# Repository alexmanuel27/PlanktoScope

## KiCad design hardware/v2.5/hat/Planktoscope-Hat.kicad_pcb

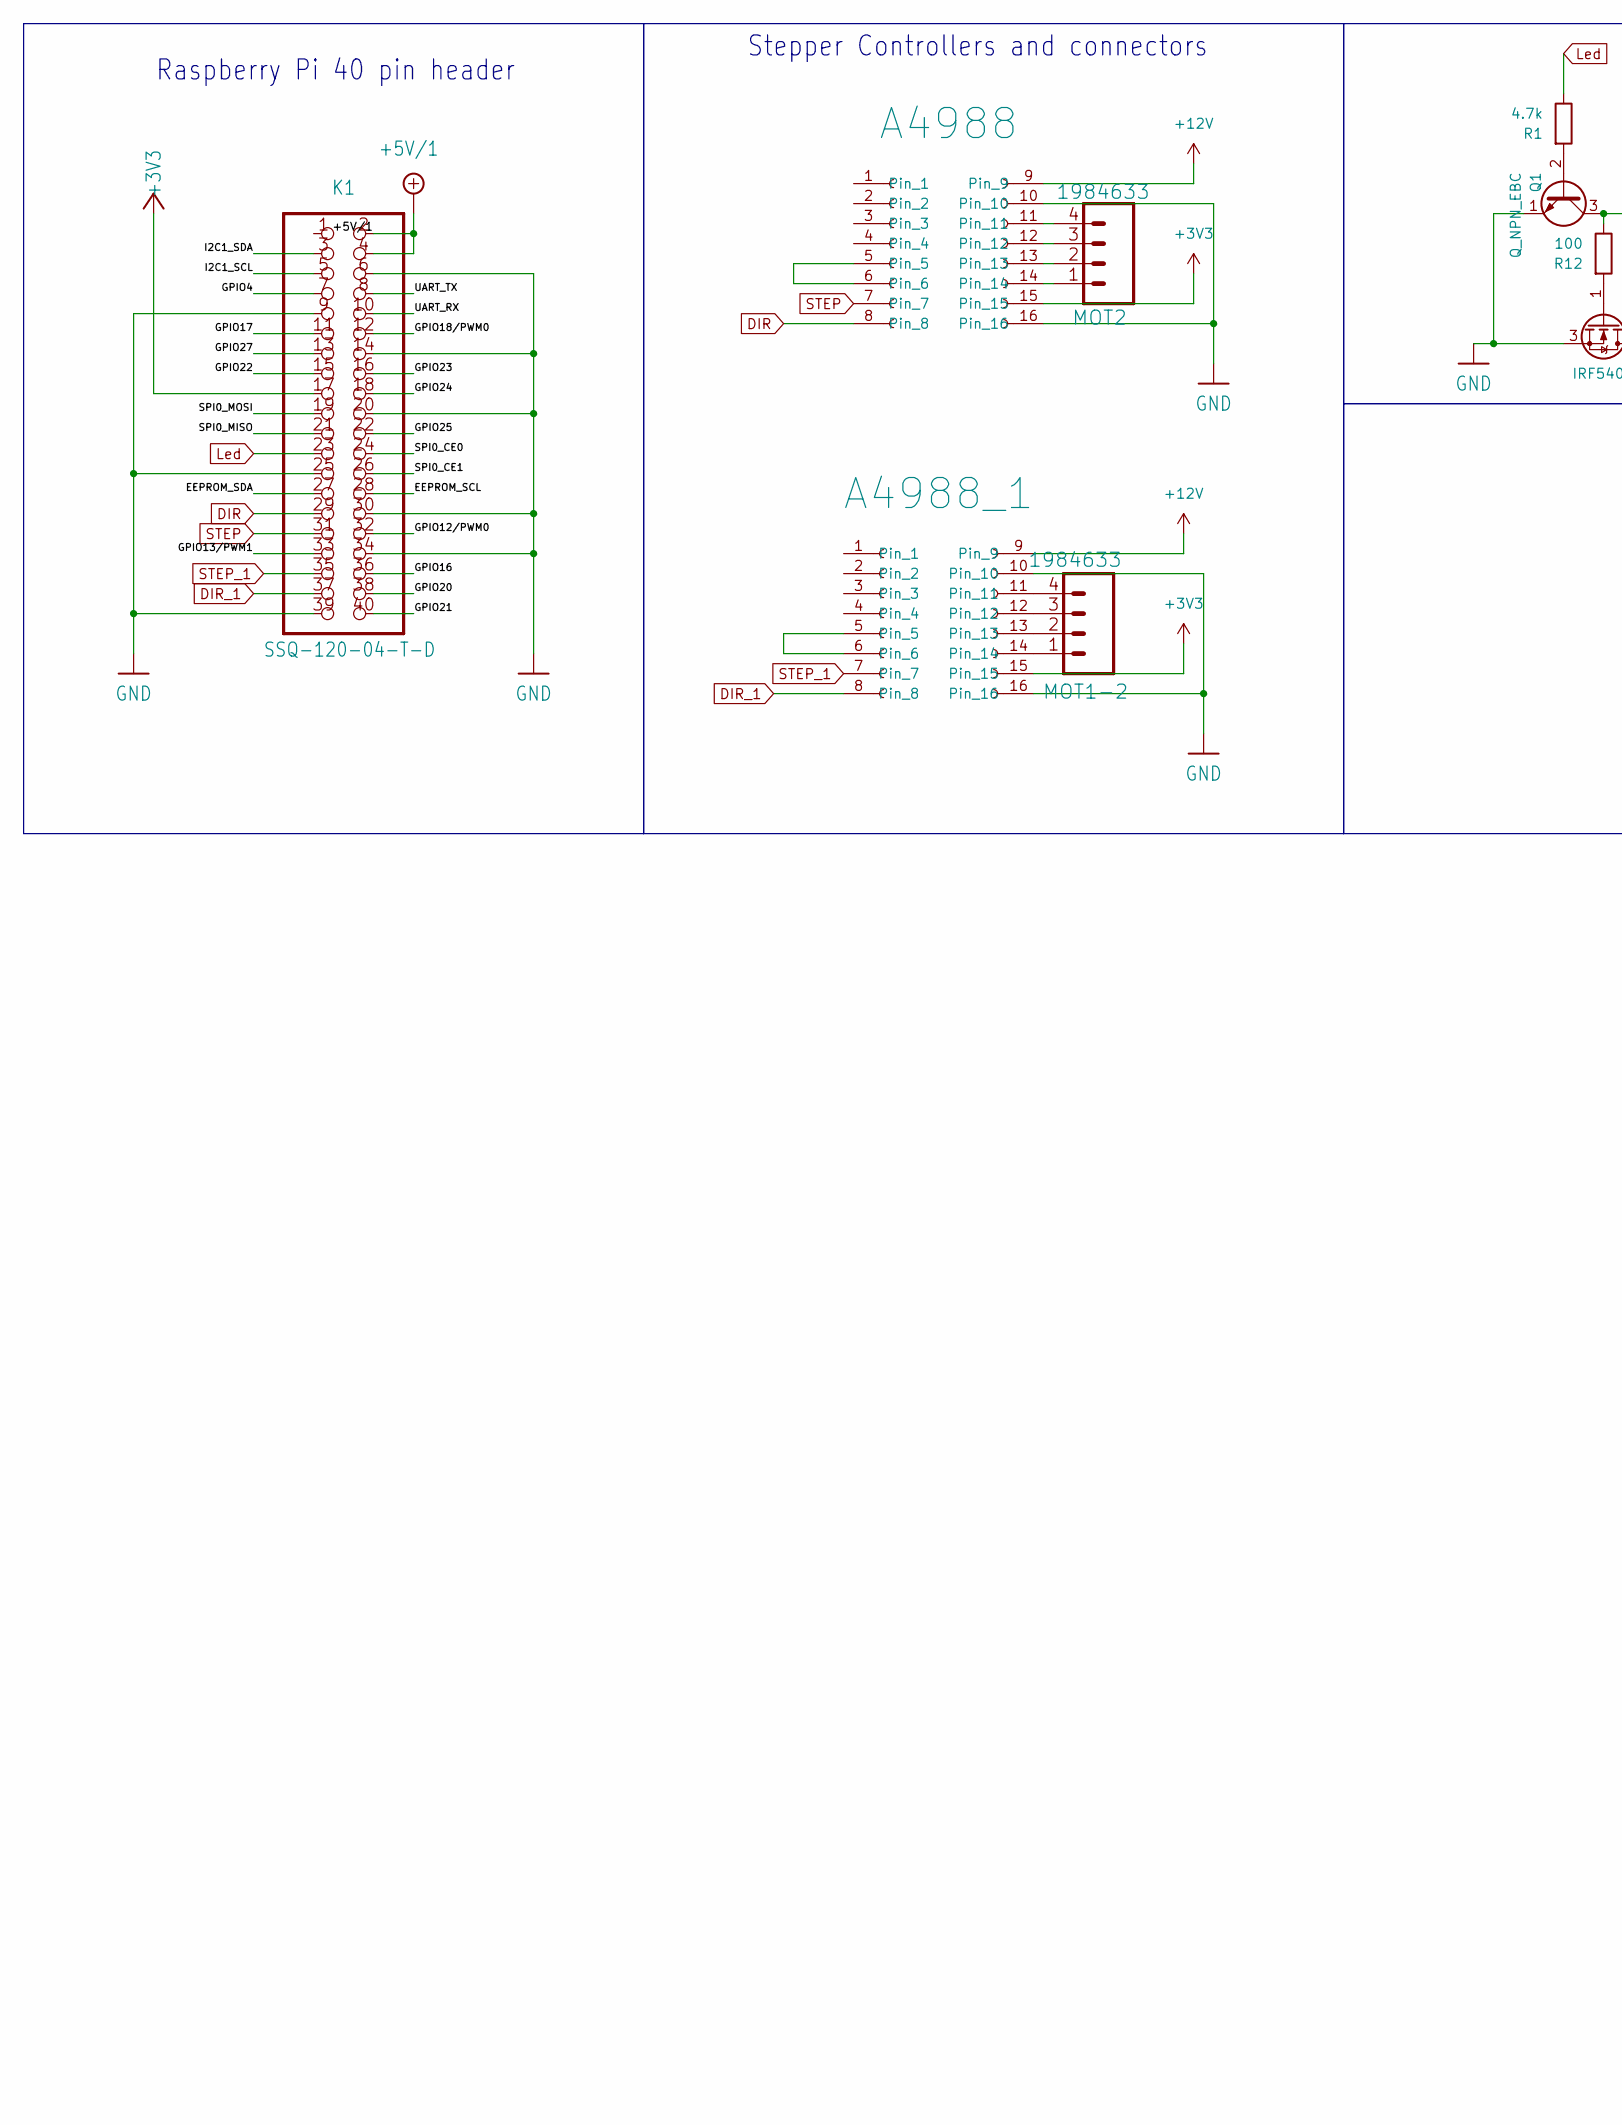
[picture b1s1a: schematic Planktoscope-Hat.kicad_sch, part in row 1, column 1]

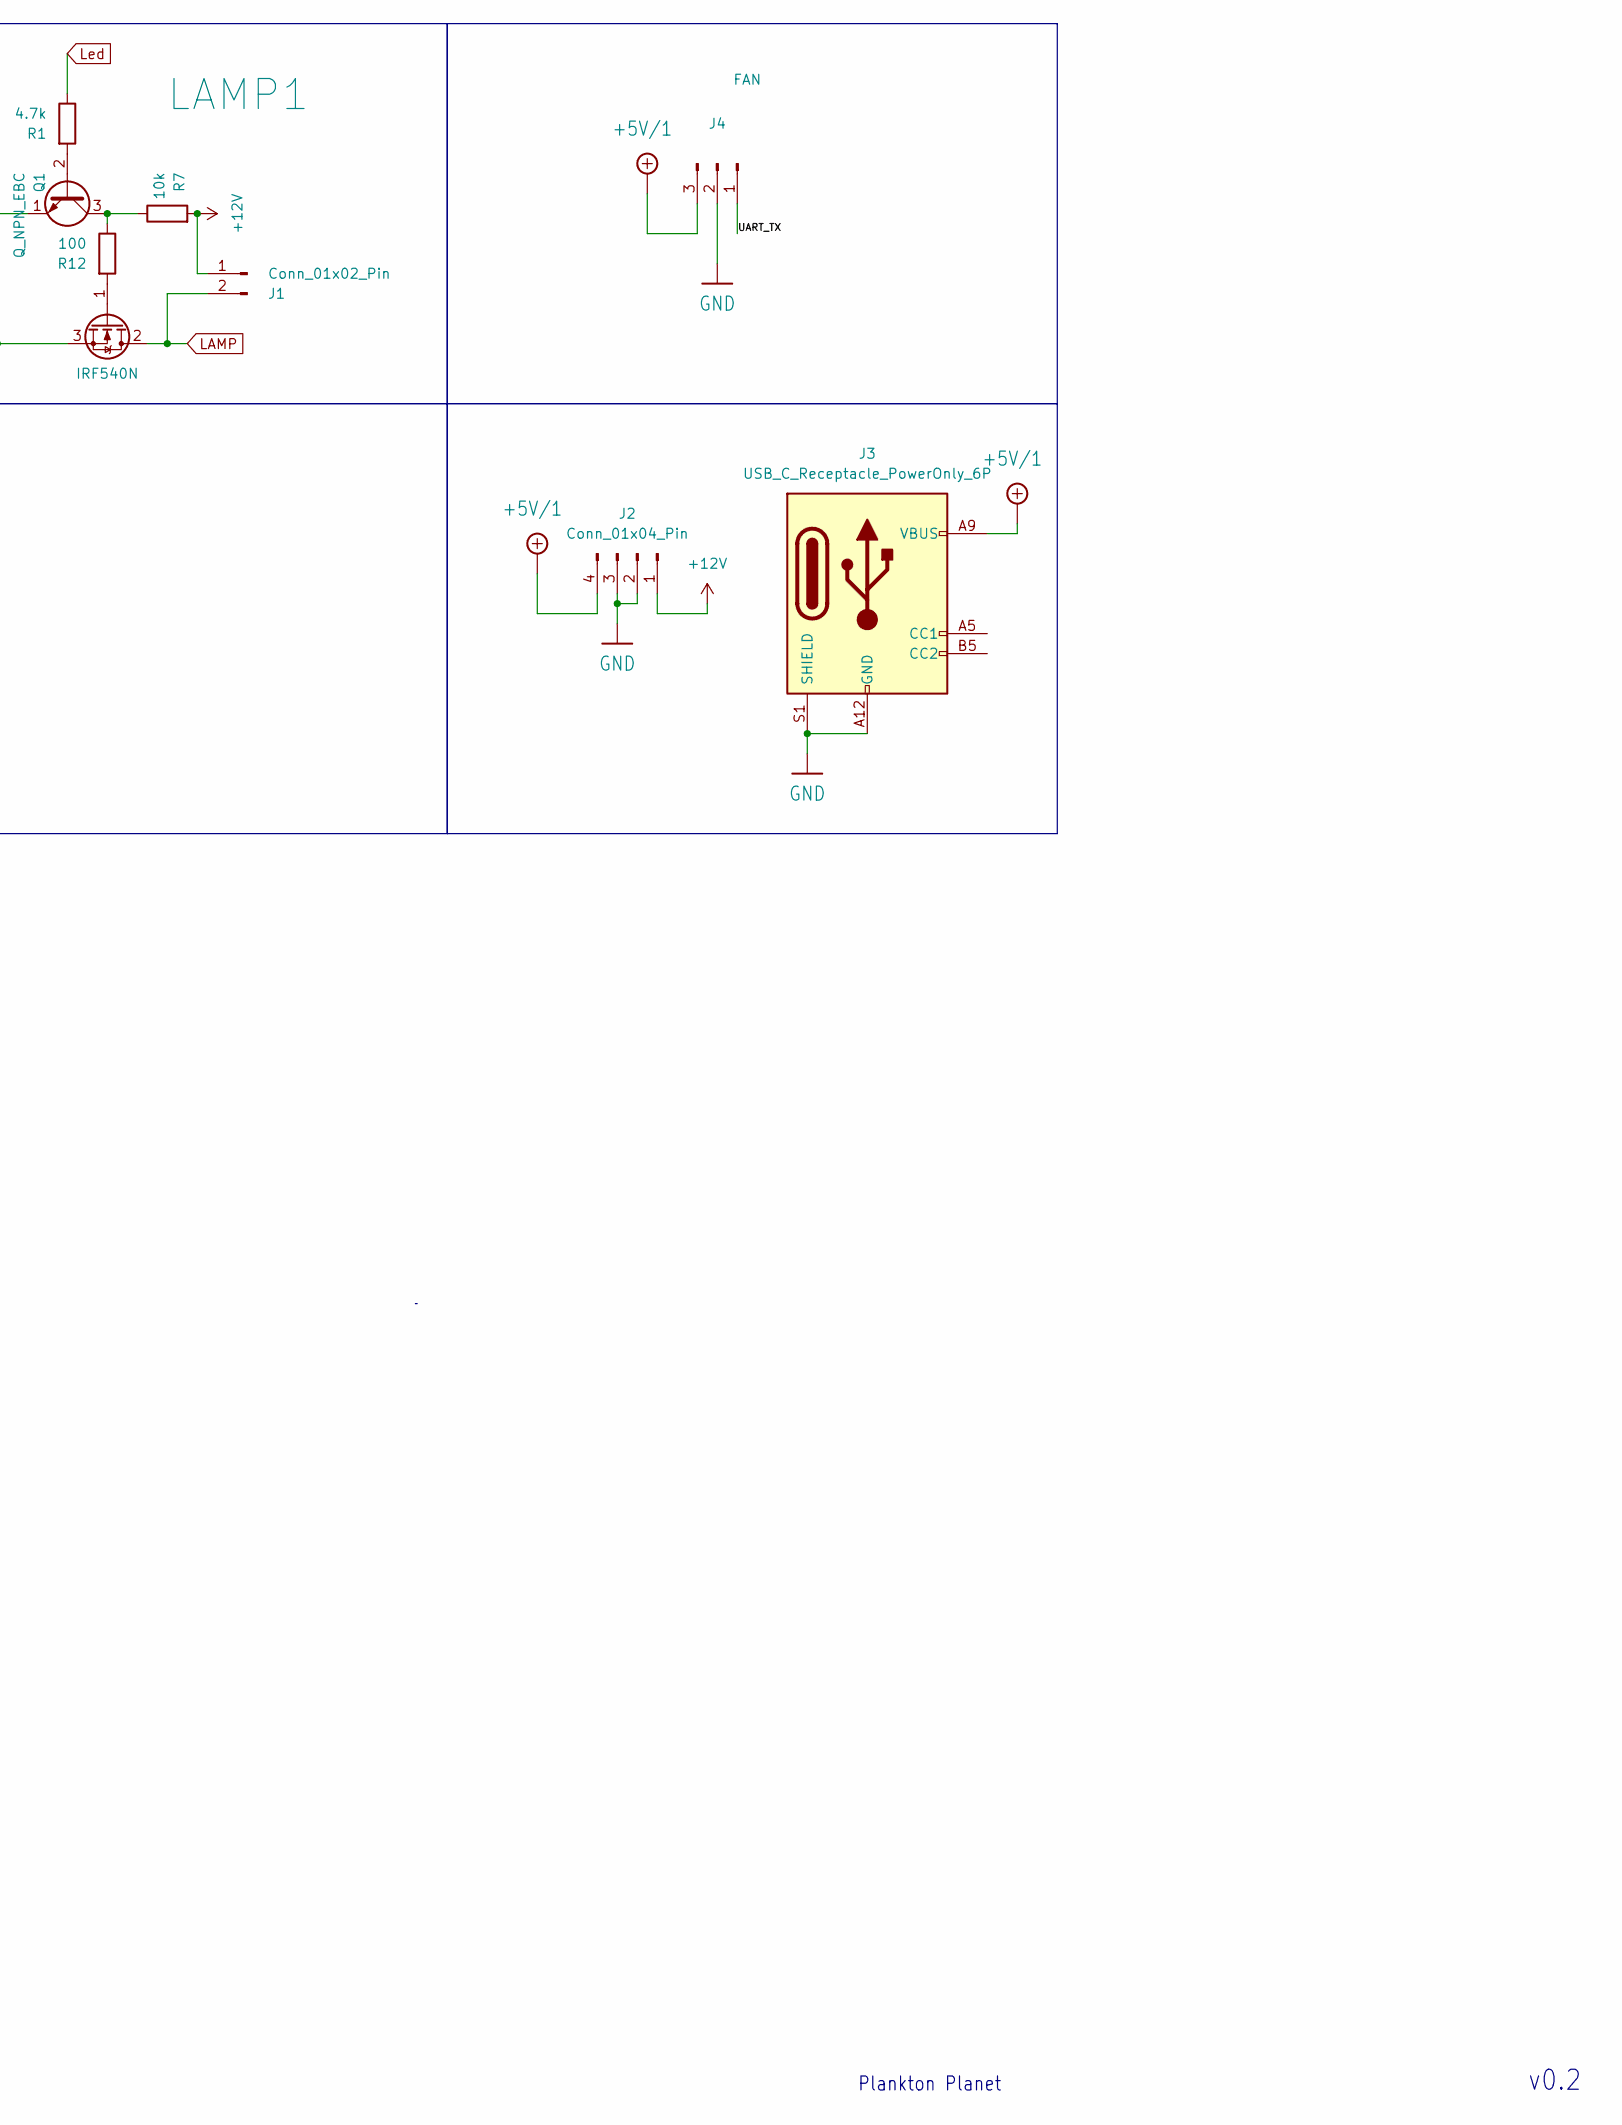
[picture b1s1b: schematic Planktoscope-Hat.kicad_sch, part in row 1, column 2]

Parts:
A4988, A4988_1: POLOLU_SMD
J1: Conn_01x02_Pin; PinHeader_1x02_P2.54mm_Horizontal
J2: Conn_01x04_Pin; dc-dc up
J3: USB_C_Receptacle_PowerOnly_6P; USB_C_Receptacle_GCT_USB4135-GF-A_6P_TopMnt_Horizontal
J4: FAN; PinHeader_1x03_P2.54mm_Horizontal
K1: SSQ-120-04-T-D; Raspberry_Pi_Zero_Socketed_THT_FaceDown_MountingHoles
LAMP1: IRF540N; TO-263-2
MOT1-2, MOT2: 1984633; PinHeader_1x04_P2.54mm_Horizontal
Q1: Q_NPN_EBC; TO-92L_Inline_Wide
R1: 4.7k; D_1206_3216Metric
R7: 10k; D_1206_3216Metric
R12: 100; D_1206_3216Metric

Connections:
+3V3: A4988.15, A4988_1.15, K1.17
+5V/1: J2.4, J3.A9 (VBUS), J3.B9 (VBUS), J4.3, K1.2, K1.4
+12V: A4988.9, A4988_1.9, J1.1, J2.1, R7.2
/EEPROM_SCL: K1.28
/EEPROM_SDA: K1.27
/GPIO4: K1.7
/GPIO12/PWM0: K1.32
/GPIO13/PWM1: K1.33
/GPIO16: K1.36
/GPIO17: K1.11
/GPIO18/PWM0: K1.12
/GPIO20: K1.38
/GPIO21: K1.40
/GPIO22: K1.15
/GPIO23: K1.16
/GPIO24: K1.18
/GPIO25: K1.22
/GPIO27: K1.13
/I2C1_SCL: K1.5
/I2C1_SDA: K1.3
/SPI0_CE0: K1.24
/SPI0_CE1: K1.26
/SPI0_MISO: K1.21
/SPI0_MOSI: K1.19
/UART_RX: K1.10
/UART_TX: J4.1, K1.8
DIR: A4988.8, K1.29
DIR_1: A4988_1.8, K1.37
GND: A4988.10, A4988.16, A4988_1.10, A4988_1.16, J2.2, J2.3, J3.A12 (GND), J3.B12 (GND), J3.S1 (SHIELD), J4.2, K1.6, K1.9, K1.14, K1.20, K1.25, K1.30, K1.34, K1.39, LAMP1.3 (S), Q1.1 (E)
LAMP: J1.2, LAMP1.2 (D)
Led: K1.23, R1.1
unnamed: A4988.5, A4988.6
unnamed: A4988.11, MOT2.4
unnamed: A4988.12, MOT2.3
unnamed: A4988.13, MOT2.2
unnamed: A4988.14, MOT2.1
unnamed: A4988_1.5, A4988_1.6
unnamed: A4988_1.11, MOT1-2.4
unnamed: A4988_1.12, MOT1-2.3
unnamed: A4988_1.13, MOT1-2.2
unnamed: A4988_1.14, MOT1-2.1
unnamed: LAMP1.1 (G), R12.2
unnamed: Q1.2 (B), R1.2
unnamed: Q1.3 (C), R7.1, R12.1
STEP: A4988.7, K1.31
STEP_1: A4988_1.7, K1.35

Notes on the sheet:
Stepper Controllers and connectors
v0.2
Plankton Planet
Raspberry Pi 40 pin header

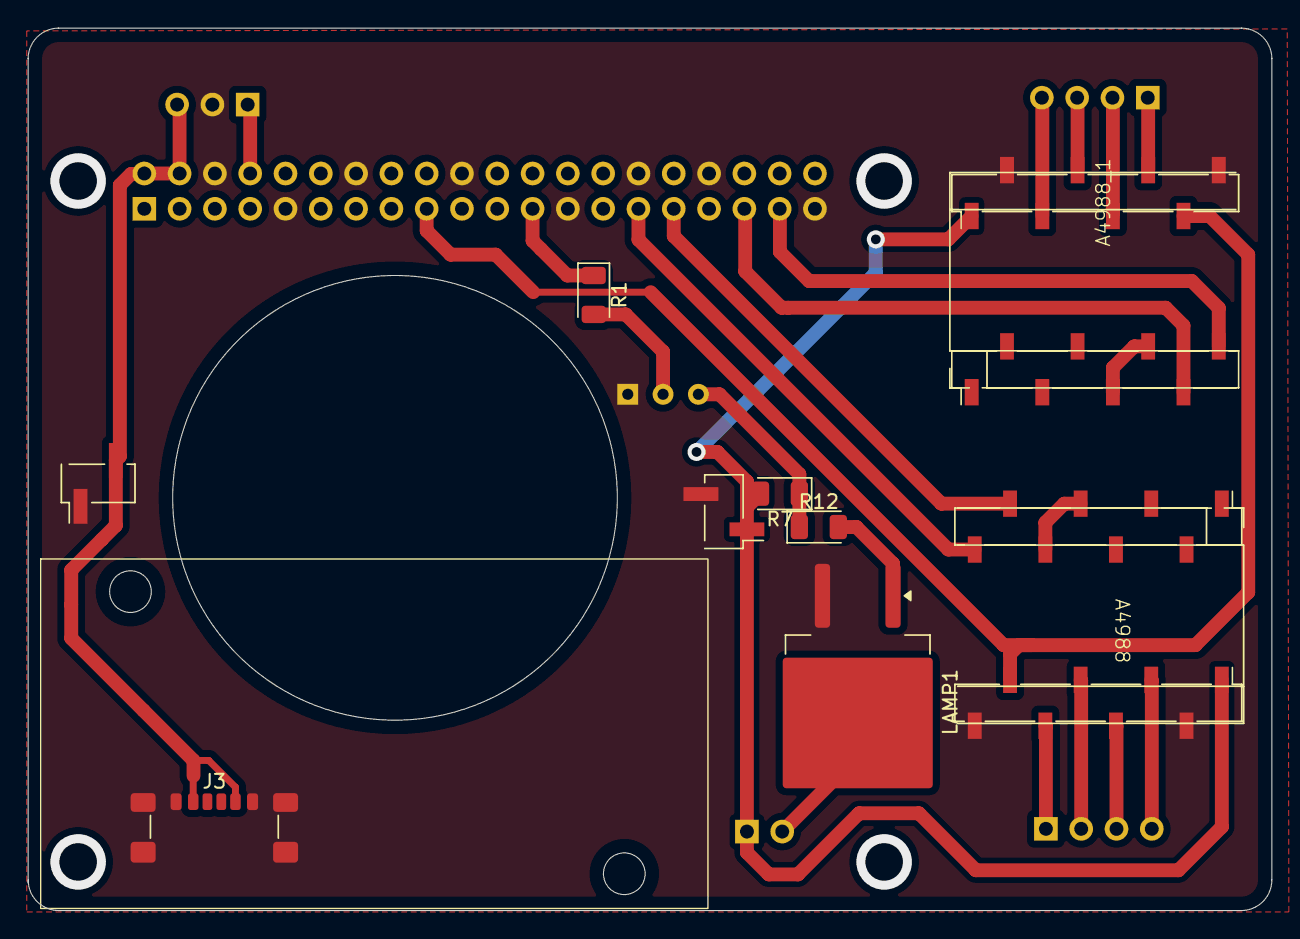
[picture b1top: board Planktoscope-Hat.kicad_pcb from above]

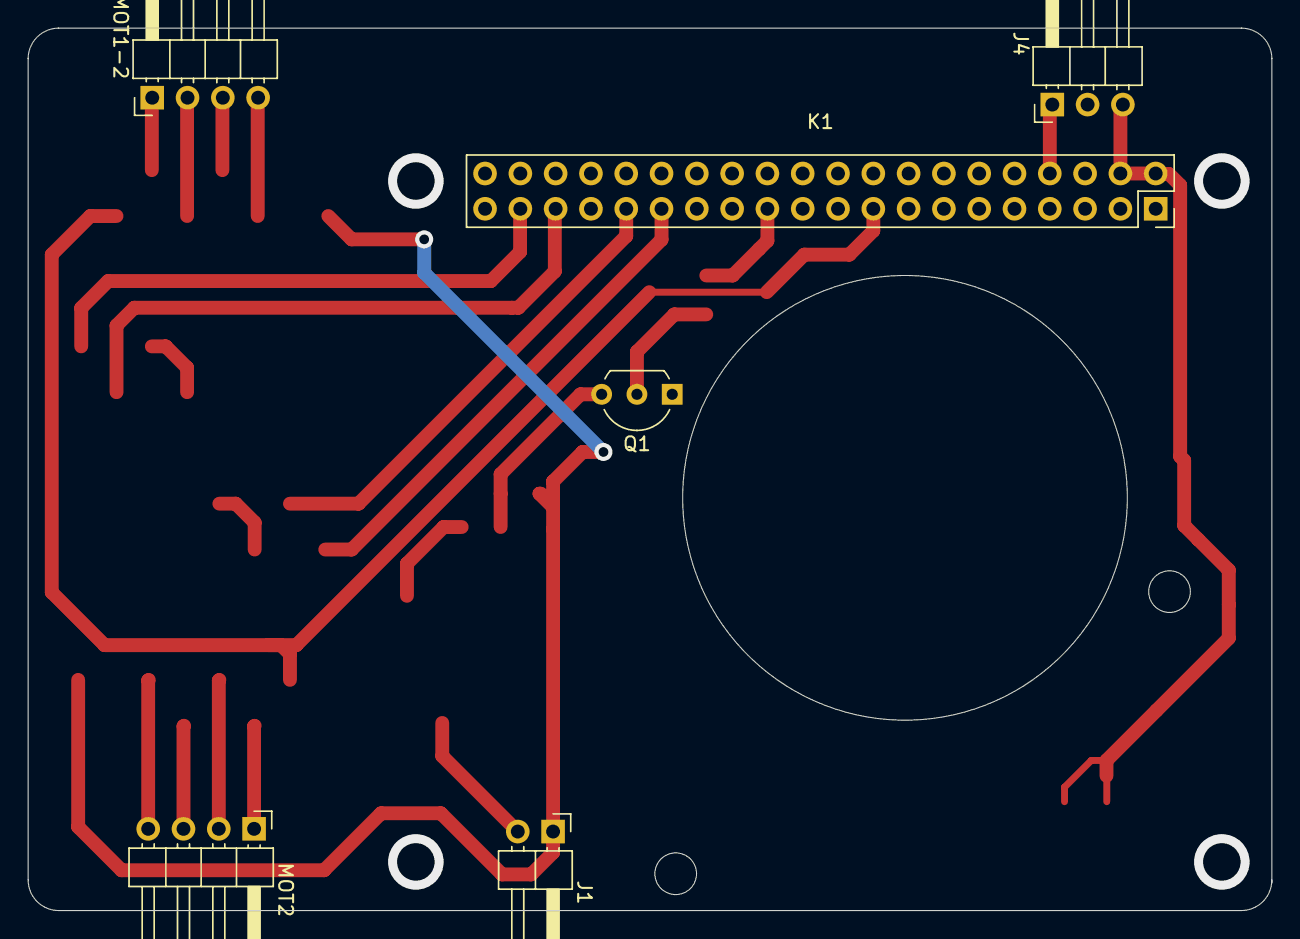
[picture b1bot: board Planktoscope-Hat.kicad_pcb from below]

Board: 2 copper layers, 89.5 x 63.5 mm, 14 parts (6 on the bottom side), 24 nets.

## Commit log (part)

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2025-11-05 new board
2025-11-14 PCB v2
2025-12-02 first commint in this repo
2025-12-05 antes de polonia
2025-12-05 limpieza
2025-12-26 all ready(list ok)
2026-01-15 css and bash
2026-01-16 nada
